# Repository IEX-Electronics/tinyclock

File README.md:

# tinyclock

## What is this?
This tinyclock was designed to be placed on top of my Bambu Lab H2S using power from the USB port. (Yes, I know, it's janky), but since my room doesn't have a clock or other
timekeeping mechanism, and the printer doesn't have one, I thought it would be pretty nifty to have a little no-controls 4-segment display clock (using bluetooth/wifi for initial setup)
to connect to the internet to NTP servers such as time.apple.com, which automatically set date/time based on IP. (No need to reset for daylight savings time). Originally, I also intended
to make a USB to dual USB adapter, but I ran out of budget for tier 4. 

## Concept Sketches

PCB with resistors added. I don't have any 3D model for seeed studio rp2040 nor the 7-segment display, but this is how it should look, (roughly)

Chassis with connetor body (this makes sure that it can stay upright.

PCB Layout... It's not the prettiest, but it gets the job done, and is clean (enough)

3D models of the final PCB. I don't really have 3D models available for either the XIAO RP-2040 nor the 7-segment display, but, you get the idea.

## Side Note
Hellos, I don't quite have a great idea for the size of chassis yet, as I don't have 3D models of the components listed above, but once I recieve the components and is able to measure myself, the rest of the process will probably go a lot smoother.

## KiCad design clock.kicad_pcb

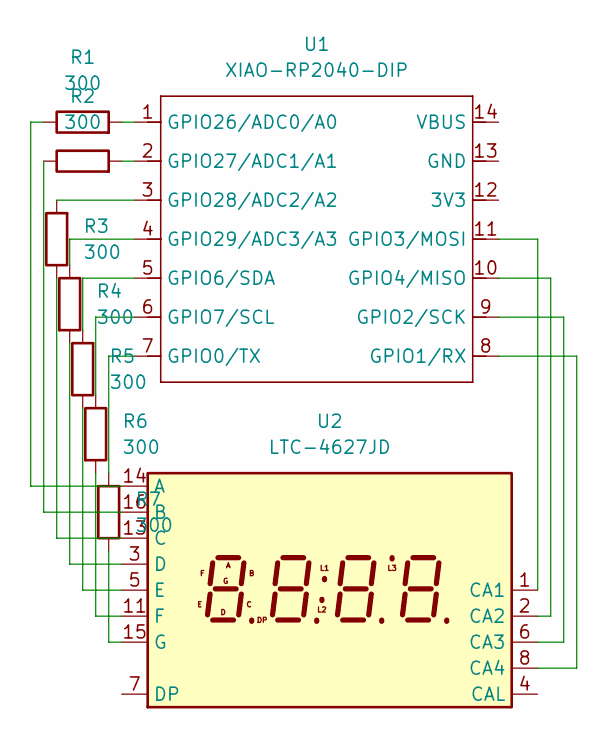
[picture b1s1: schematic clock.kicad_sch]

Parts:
R1, R2, R3, R4, R5, R6, R7: 300; R_Axial_DIN0207_L6.3mm_D2.5mm_P7.62mm_Horizontal
U1: XIAO-RP2040-DIP
U2: LTC-4627JD; LTC-4627Jx

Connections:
unnamed: R7.2, U1.7 (GPIO0/TX)
unnamed: U1.8 (GPIO1/RX), U2.8 (CA4)
unnamed: U1.9 (GPIO2/SCK), U2.6 (CA3)
unnamed: U1.11 (GPIO3/MOSI), U2.1 (CA1)
unnamed: U1.10 (GPIO4/MISO), U2.2 (CA2)
unnamed: R5.2, U1.5 (GPIO6/SDA)
unnamed: R6.1, U1.6 (GPIO7/SCL)
unnamed: R1.2, U1.1 (GPIO26/ADC0/A0)
unnamed: R2.2, U1.2 (GPIO27/ADC1/A1)
unnamed: R3.2, U1.3 (GPIO28/ADC2/A2)
unnamed: R4.1, U1.4 (GPIO29/ADC3/A3)
unnamed: R1.1, U2.14 (A)
unnamed: R2.1, U2.16 (B)
unnamed: R3.1, U2.13 (C)
unnamed: R4.2, U2.3 (D)
unnamed: R5.1, U2.5 (E)
unnamed: R6.2, U2.11 (F)
unnamed: R7.1, U2.15 (G)

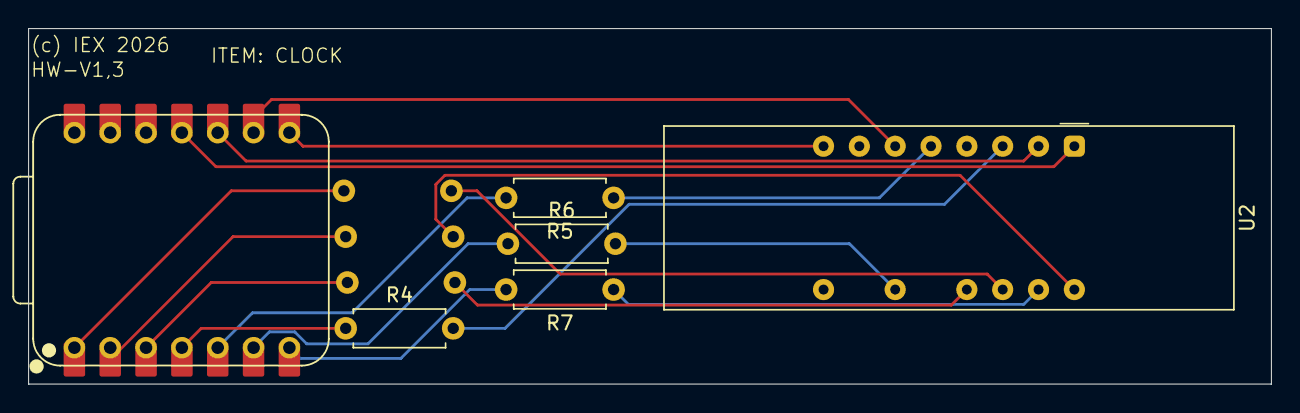
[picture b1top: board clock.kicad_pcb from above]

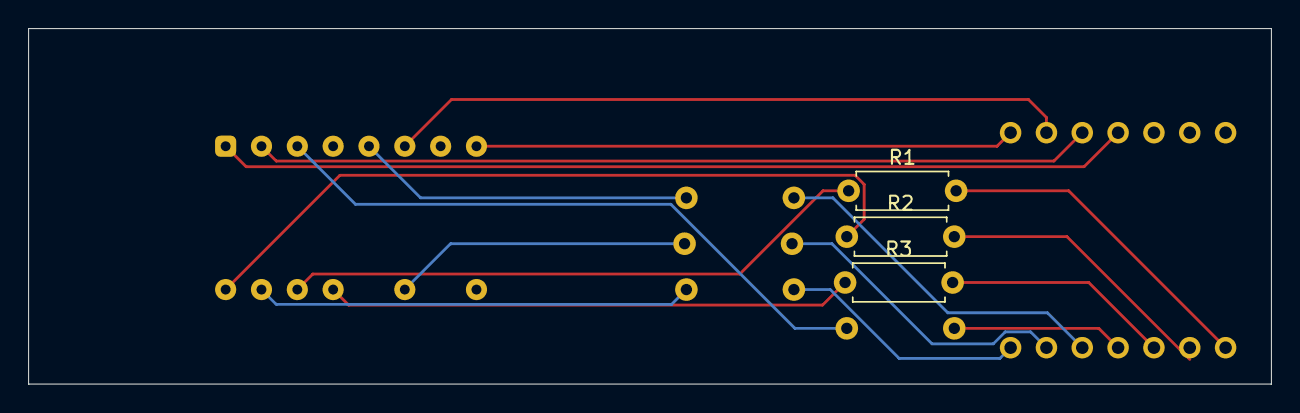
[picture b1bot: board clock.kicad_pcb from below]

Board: 2 copper layers, 88.1 x 25.2 mm, 9 parts (3 on the bottom side), 18 nets.

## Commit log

2026-01-06 init
2026-01-09 Create README.md for tinyclock project
    Added a README file explaining the tinyclock project and its purpose.
2026-01-09 Update README with chassis image for stability
    Added an image of the chassis with connector body to ensure upright stability.
2026-01-12 Update README with budget and design details
    Clarified budget constraints for USB adapter and added additional PCB layout and 3D model images.
2026-01-12 stuff
